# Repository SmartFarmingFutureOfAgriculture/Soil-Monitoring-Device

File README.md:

# Smart Farming Soil Monitoring Device
This is an **open-source soil monitoring system** designed to measure NPK levels, temperature, moisture, and conductivity.

🚧 **Project Status: In Development** 🚧  
This project is still in the **development phase** and may change frequently.  
Some features may not be fully implemented, and modifications are ongoing.  
Contributions and feedback are welcome!  

## License
- **Software**: GNU GPL-2.0  
- **Hardware**: CERN OHL  
- **Disclaimer**: This project is provided **"as is"**, without any warranty or liability.

## How to Contribute
Contributions are welcome! Please follow the licensing rules and give proper attribution.

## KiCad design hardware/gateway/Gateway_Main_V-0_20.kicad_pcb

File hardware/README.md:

## 🛠️ Hardware Development Tools
The hardware design files were created using:

- **KiCAD 6.x+** (for schematics & PCB design) → [https://www.kicad.org/](https://www.kicad.org/)
- **FreeCAD** (for 3D enclosure modeling) → [https://www.freecadweb.org/](https://www.freecadweb.org/)

💡 To modify the hardware, install **KiCAD** and **FreeCAD**, then open the project files.

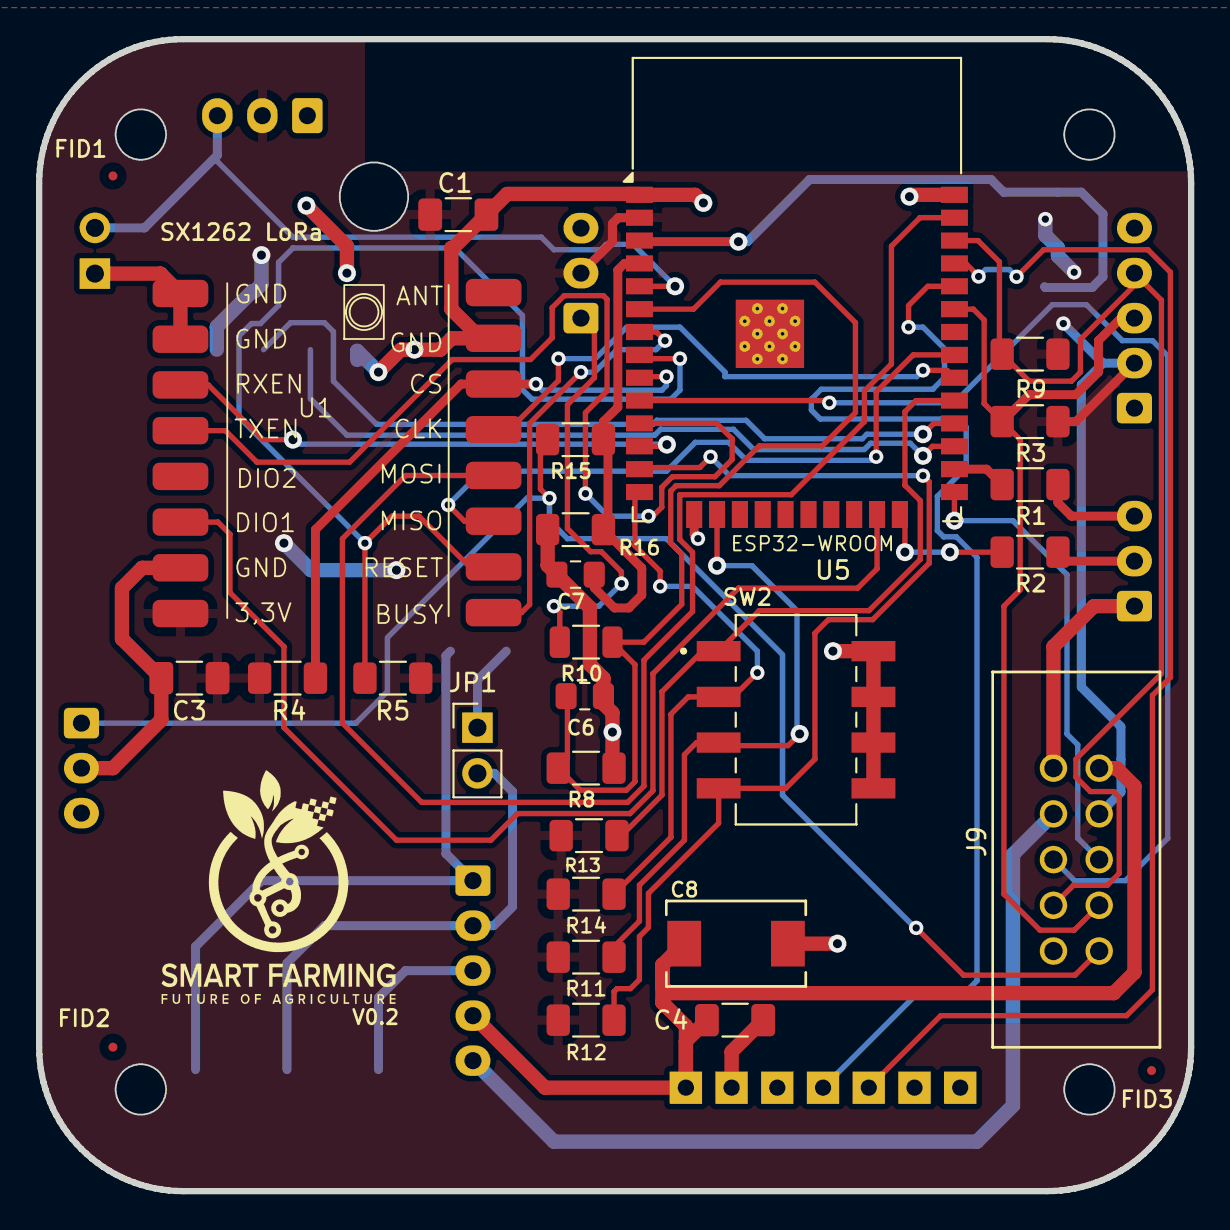
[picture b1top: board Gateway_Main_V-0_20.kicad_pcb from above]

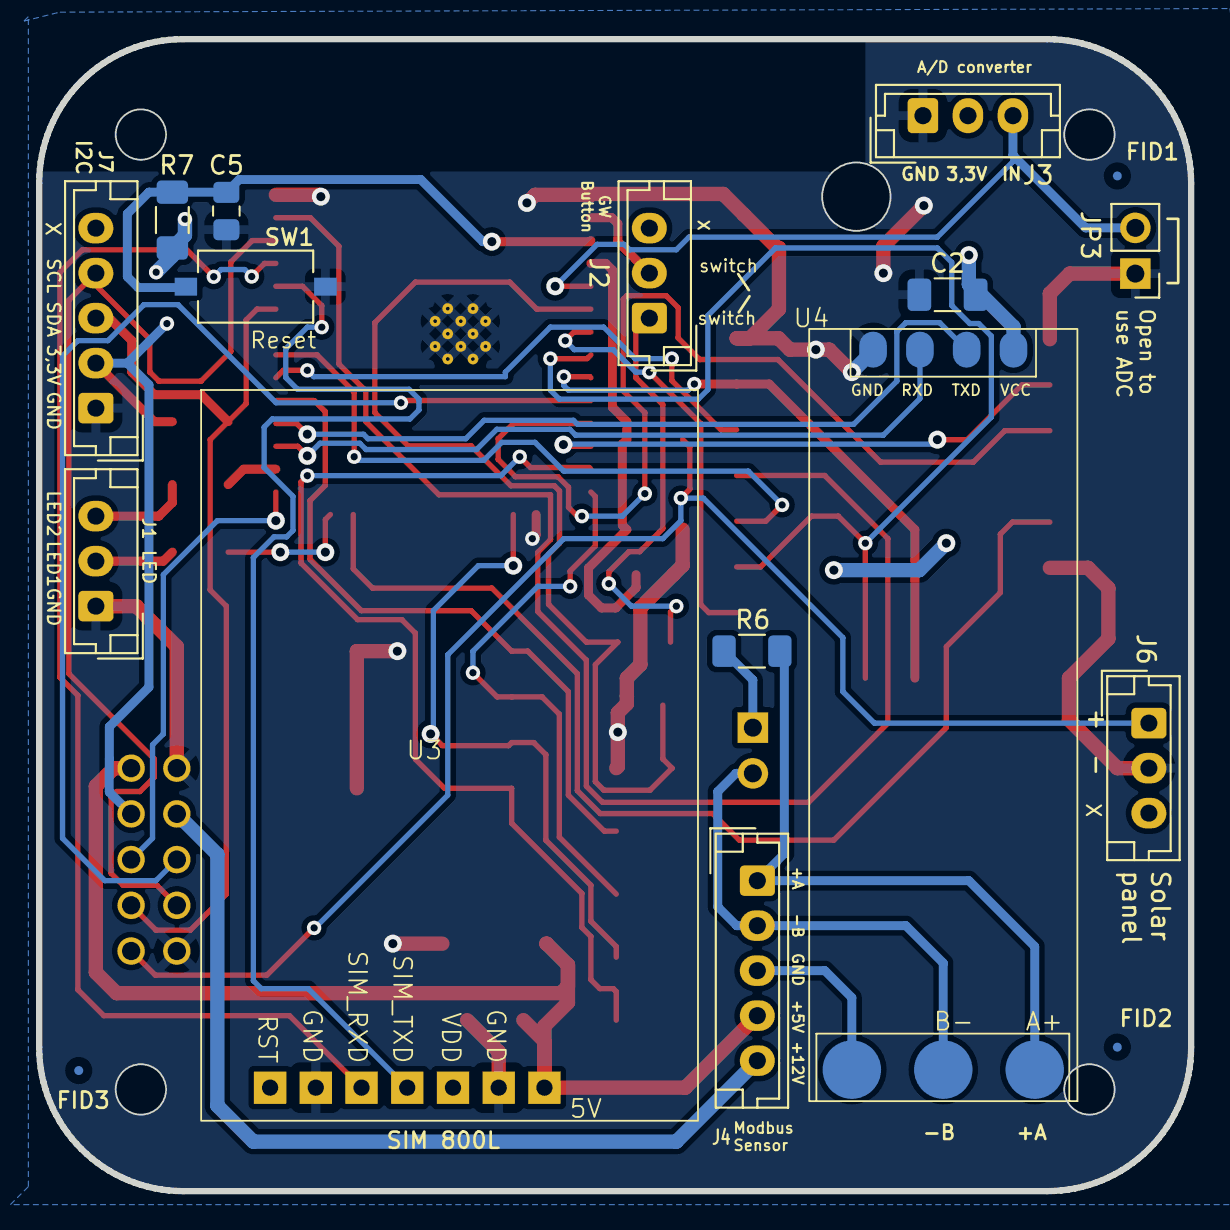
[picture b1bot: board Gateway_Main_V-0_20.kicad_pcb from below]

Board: 2 copper layers, 64.0 x 64.0 mm, 45 parts (17 on the bottom side), 39 nets.

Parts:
C1, C2, C3: 10uF X7R Ceramic; C_1206_3216Metric_Pad1.33x1.80mm_HandSolder
C4: 100uF; C_1206_3216Metric_Pad1.33x1.80mm_HandSolder
C5: 1uF; C_0805_2012Metric_Pad1.18x1.45mm_HandSolder
C6, C7: 0.1uF; C_0805_2012Metric_Pad1.18x1.45mm_HandSolder
C8: 470uF; TAJD_AVX
FID1, FID1#2, FID2, FID2#2, FID3, FID3#2: Fiducial; Fiducial_0.5mm_Mask1.5mm
J1: LED; JST_EH_B3B-EH-A_1x03_P2.50mm_Vertical
J2: Gateway button; JST_EH_B3B-EH-A_1x03_P2.50mm_Vertical
J3: A/D converter; JST_EH_B3B-EH-A_1x03_P2.50mm_Vertical
J4: Modbus (Sensor); JST_EH_B5B-EH-A_1x05_P2.50mm_Vertical
J6: Solar module; JST_EH_B3B-EH-A_1x03_P2.50mm_Vertical
J7: I2C; JST_EH_B5B-EH-A_1x05_P2.50mm_Vertical
J9: 302-S101; CONN10_302-S101_OST
JP1: Jumper_2_Bridged; PinHeader_1x02_P2.54mm_Vertical
JP3: ADC1_CH3; PinHeader_1x02_P2.54mm_Vertical
R1, R2: 150; R_1206_3216Metric_Pad1.30x1.75mm_HandSolder
R3, R9: 10k; R_1206_3216Metric_Pad1.30x1.75mm_HandSolder
R4, R5, R7: 47k; R_1206_3216Metric_Pad1.30x1.75mm_HandSolder
R6: 120; R_1206_3216Metric_Pad1.30x1.75mm_HandSolder
R8: 100k; R_1206_3216Metric_Pad1.30x1.75mm_HandSolder
R10: 47k; R_1206_3216Metric
R11, R12, R13, R14: 82k; R_1206_3216Metric_Pad1.30x1.75mm_HandSolder
R15: 20k 1%; R_1206_3216Metric_Pad1.30x1.75mm_HandSolder
R16: 30k 1%; R_1206_3216Metric_Pad1.30x1.75mm_HandSolder
SW1: Reset; SW_Tactile_SPST_NO_Straight_CK_PTS636Sx25SMTRLFS
SW2: SW-219-4MST; Switch-SW_219-4MST
U1: CORE1262-868M; SX1262_LoRa_NODE
U3: SIM800L; SIM800L_EVB-MODULE
U4: TTL to RS485; RS485_To_TTL
U5: ESP32-WROOM-32E; ESP32-WROOM-32D

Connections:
+3.3V: C1.1, C2.1, C3.1, J2.2, J3.2, J7.2, J9.7, R3.1, R4.1, R5.1, R7.1, R9.1, R11.1, R12.1, R13.1, R14.1, U1.8 (3V3), U4.4 (Vcc), U5.2 (VDD)
+5V: C4.1, C8.1, J4.4, J9.9, U3.1 (5V)
+12V: J4.5, J9.8
GND: C1.2, C2.2, C3.2, C4.2, C5.2, C6.2, C7.2, C8.2, J1.1, J3.1, J6.2, J7.1, J9.2, J9.10, JP3.1 (A), R8.2, R16.2, SW1.2, SW2.5, SW2.6, SW2.7, SW2.8, U1.1 (GND), U1.2 (GND), U1.7 (GND), U1.15 (GND), U3.2 (GND), U3.6 (GND), U4.1 (GND), U5.1 (GND), U5.15 (GND), U5.38 (GND), U5.39 (GND)
unnamed: J1.2, R2.2
unnamed: J1.3, R1.2
unnamed: J2.1, R10.1
unnamed: J3.3, JP3.2 (B), U5.5 (SENSOR_VN)
unnamed: J4.1, R6.2, U4.5 (A+)
unnamed: J4.2, JP1.2 (B), U4.6 (B-)
unnamed: J4.3, U4.7 (GND2)
unnamed: J6.1, J9.1, R15.1
unnamed: J7.3, J9.3, R3.2, U5.33 (IO21)
unnamed: J7.4, J9.4, R9.2, U5.36 (IO22)
unnamed: JP1.1 (A), R6.1
unnamed: U1.9 (BUSY), U5.7 (IO35)
unnamed: U1.13 (CLK), U5.30 (IO18)
unnamed: R4.2, U1.14 (CS), U5.9 (IO33)
unnamed: U1.6 (DIO1), U5.23 (IO15)
unnamed: U1.11 (MISO), U5.31 (IO19)
unnamed: U1.12 (MOSI), U5.37 (IO23)
unnamed: R5.2, U1.10 (RESET), U5.8 (IO32)
unnamed: U1.3 (RXEN), U5.12 (IO27)
unnamed: U1.4 (TXEN), U5.11 (IO26)
unnamed: U3.5 (SIM_RXD), U5.35 (TXD0/IO1)
unnamed: U3.4 (SIM_TXD), U5.34 (RXD0/IO3)
unnamed: U4.2 (RxD), U5.27 (IO16)
unnamed: U4.3 (TxD), U5.28 (IO17)
unnamed: C5.1, R7.2, SW1.1, U5.3 (EN)
unnamed: J9.5, U5.25 (IO0)
unnamed: R2.1, U5.24 (IO2)
unnamed: R1.1, U5.26 (IO4)
unnamed: R13.2, SW2.1, U5.29 (IO5)
unnamed: R14.2, SW2.2, U5.14 (IO12)
unnamed: R11.2, SW2.3, U5.16 (IO13)
unnamed: R12.2, SW2.4, U5.13 (IO14)
unnamed: J9.6, U5.10 (IO25)
unnamed: C6.1, R8.1, R10.2, U5.6 (IO34)
unnamed: C7.1, R15.2, R16.1, U5.4 (SENSOR_VP)

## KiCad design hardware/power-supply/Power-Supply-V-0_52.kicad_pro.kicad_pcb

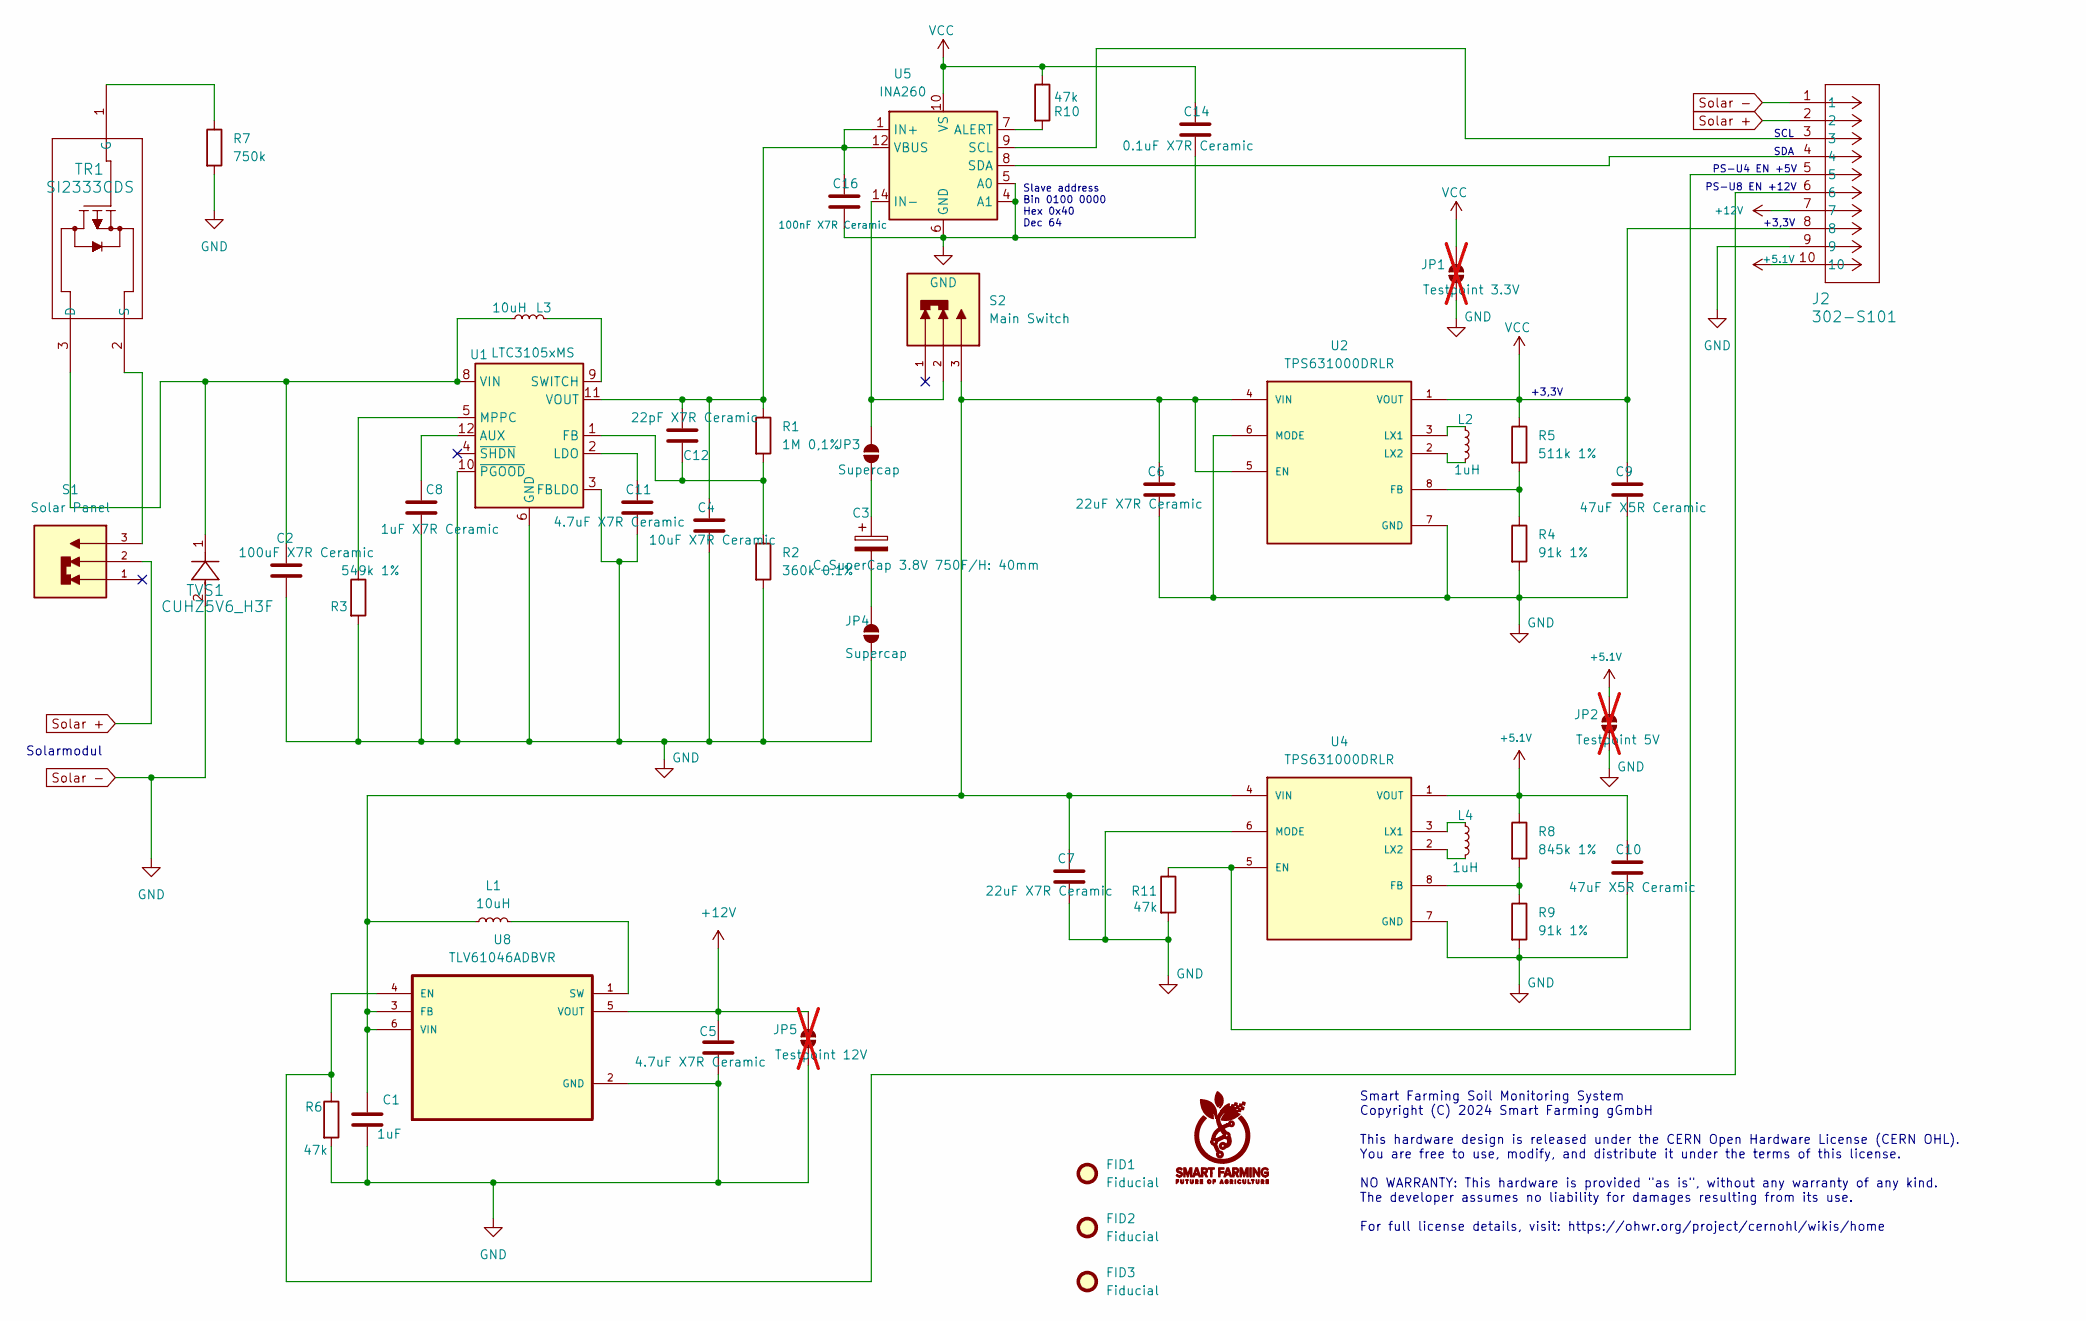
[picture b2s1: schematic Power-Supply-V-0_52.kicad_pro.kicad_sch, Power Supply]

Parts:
C1: 1uF; C_0805_2012Metric_Pad1.18x1.45mm_HandSolder
C2: 100uF X7R Ceramic; C_1206_3216Metric_Pad1.33x1.80mm_HandSolder
C3: C_SuperCap 3.8V 750F/H: 40mm; CP_Radial_D18.0mm_P7.50mm
C4: 10uF X7R Ceramic; C_1206_3216Metric_Pad1.33x1.80mm_HandSolder
C5, C11: 4.7uF X7R Ceramic; C_0805_2012Metric_Pad1.18x1.45mm_HandSolder
C6, C7: 22uF X7R Ceramic; C_1206_3216Metric_Pad1.33x1.80mm_HandSolder
C8: 1uF X7R Ceramic; C_0805_2012Metric_Pad1.18x1.45mm_HandSolder
C9, C10: 47uF X5R Ceramic; C_1206_3216Metric_Pad1.33x1.80mm_HandSolder
C12: 22pF X7R Ceramic; C_0805_2012Metric_Pad1.18x1.45mm_HandSolder
C14: 0.1uF X7R Ceramic; C_0805_2012Metric_Pad1.18x1.45mm_HandSolder
C16: 100nF X7R Ceramic; C_0805_2012Metric_Pad1.18x1.45mm_HandSolder
FID1, FID2, FID3: Fiducial; Fiducial_0.75mm_Mask1.5mm
J2: 302-S101; CONN10_302-S101_OST
JP1: Testpoint 3.3V; PinHeader_1x02_P2.54mm_Vertical; not fitted
JP2: Testpoint 5V; PinHeader_1x02_P2.54mm_Vertical; not fitted
JP3, JP4: Supercap; PinHeader_1x02_P2.54mm_Vertical
JP5: Testpoint 12V; PinHeader_1x02_P2.54mm_Vertical; not fitted
L1, L3: 10uH; L_Taiyo-Yuden_MD-5050
L2, L4: 1uH; L_1008_2520Metric_Pad1.43x2.20mm_HandSolder
R1: 1M 0,1%; R_1206_3216Metric_Pad1.30x1.75mm_HandSolder
R2: 360k 0.1%; R_1206_3216Metric_Pad1.30x1.75mm_HandSolder
R3: 549k 1%; R_1206_3216Metric_Pad1.30x1.75mm_HandSolder
R4, R9: 91k 1%; R_1206_3216Metric_Pad1.30x1.75mm_HandSolder
R5: 511k 1%; R_1206_3216Metric_Pad1.30x1.75mm_HandSolder
R6, R10, R11: 47k; R_1206_3216Metric_Pad1.30x1.75mm_HandSolder
R7: 750k; R_1206_3216Metric_Pad1.30x1.75mm_HandSolder
R8: 845k 1%; R_1206_3216Metric_Pad1.30x1.75mm_HandSolder
S1: Solar Panel; SW_JS102011SCQN; PARTREV 8 Oct 21
S2: Main Switch; SW_JS102011SCQN; PARTREV 8 Oct 21
TR1: SI2333CDS; TO-236_VIS
TVS1: CUHZ5V6_H3F; SOD-323HEUS2H_TOS
U1: LTC3105xMS; MSOP-12_3x4mm_P0.65mm
U2, U4: TPS631000DRLR; SOT-583-8; PARTREV B
U5: INA260; TSSOP-16_4.4x5mm_P0.65mm
U8: TLV61046ADBVR; SOT-23-6_Handsoldering

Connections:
+5.1V: C10.1, J2.10, JP2.2 (B), R8.1, U4.1 (VOUT)
+12V: C5.1, J2.7, JP5.2 (B), U8.5 (VOUT)
unnamed: C3.1, JP3.1 (A)
unnamed: JP3.2 (B), S2.2, U5.14 (IN-), U5.15 (IN-), U5.16 (IN-)
unnamed: C3.2, JP4.2 (B)
unnamed: C2.1, L3.1, TR1.3 (D), TVS1.1, U1.8 (VIN)
unnamed: R7.1, TR1.1 (G)
unnamed: S1.3, TR1.2 (S)
unnamed: C8.1, U1.12 (AUX)
unnamed: C12.2, R1.2, R2.1, U1.1 (FB)
unnamed: C11.1, U1.2 (LDO)
unnamed: R3.1, U1.5 (MPPC)
unnamed: L3.2, U1.9 (SWITCH)
unnamed: C4.1, C12.1, C16.1, R1.1, U1.11 (VOUT), U5.1 (IN+), U5.2 (IN+), U5.3 (IN+), U5.12 (VBUS)
unnamed: C1.1, C6.1, C7.1, L1.1, S2.3, U2.4 (VIN), U2.5 (EN), U4.4 (VIN), U8.3 (FB), U8.6 (VIN)
unnamed: R4.1, R5.2, U2.8 (FB)
unnamed: L2.1, U2.3 (LX1)
unnamed: L2.2, U2.2 (LX2)
unnamed: J2.5, R11.1, U4.5 (EN)
unnamed: R8.2, R9.1, U4.8 (FB)
unnamed: L4.1, U4.3 (LX1)
unnamed: L4.2, U4.2 (LX2)
unnamed: R10.2, U5.7 (ALERT)
unnamed: J2.3, U5.9 (SCL)
unnamed: J2.4, U5.8 (SDA)
unnamed: J2.6, R6.1, U8.4 (EN)
unnamed: L1.2, U8.1 (SW)
Solar +: J2.2, S1.2
Solar -: C1.2, C2.2, C4.2, C5.2, C6.2, C7.2, C8.2, C9.2, C10.2, C11.2, C14.2, C16.2, J2.1, J2.9, JP1.1 (A), JP2.1 (A), JP4.1 (A), JP5.1 (A), R2.2, R3.2, R4.2, R6.2, R7.2, R9.2, R11.2, TVS1.2, U1.3 (FBLDO), U1.6 (GND), U1.7 (GND), U1.10 (~PGOOD), U2.6 (MODE), U2.7 (GND), U4.6 (MODE), U4.7 (GND), U5.4 (A1), U5.5 (A0), U5.6 (GND), U5.11 (GND), U8.2 (GND)
VCC: C9.1, C14.1, J2.8, JP1.2 (B), R5.1, R10.1, U2.1 (VOUT), U5.10 (VS)

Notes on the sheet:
PS-U4 EN +5V
SCL
Smart Farming Soil Monitoring System Copyright (C) 2024 Smart Farming gGmbH This hardware design is released under the CERN Open Hardware License (CERN OHL). You are free to use, modify, and distribute it under the terms of this license. NO WARRANTY: This hardware is provided "as is", without any w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
Solarmodul
SDA
PS-U8 EN +12V
Slave address Bin 0100 0000 Hex 0x40 Dec 64
+3,3V

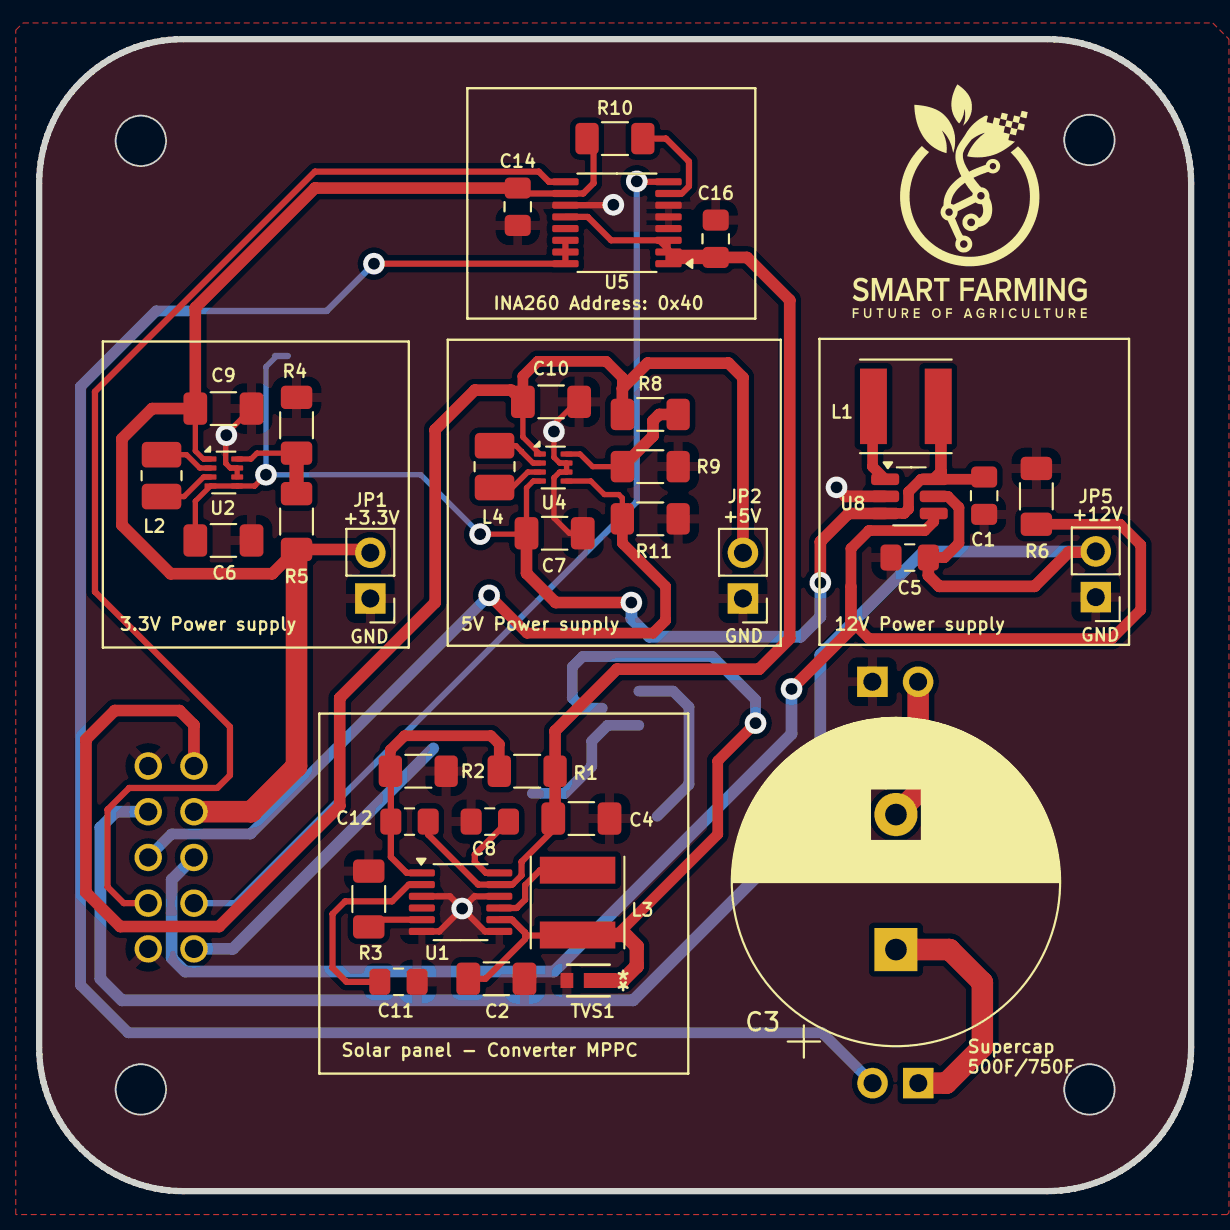
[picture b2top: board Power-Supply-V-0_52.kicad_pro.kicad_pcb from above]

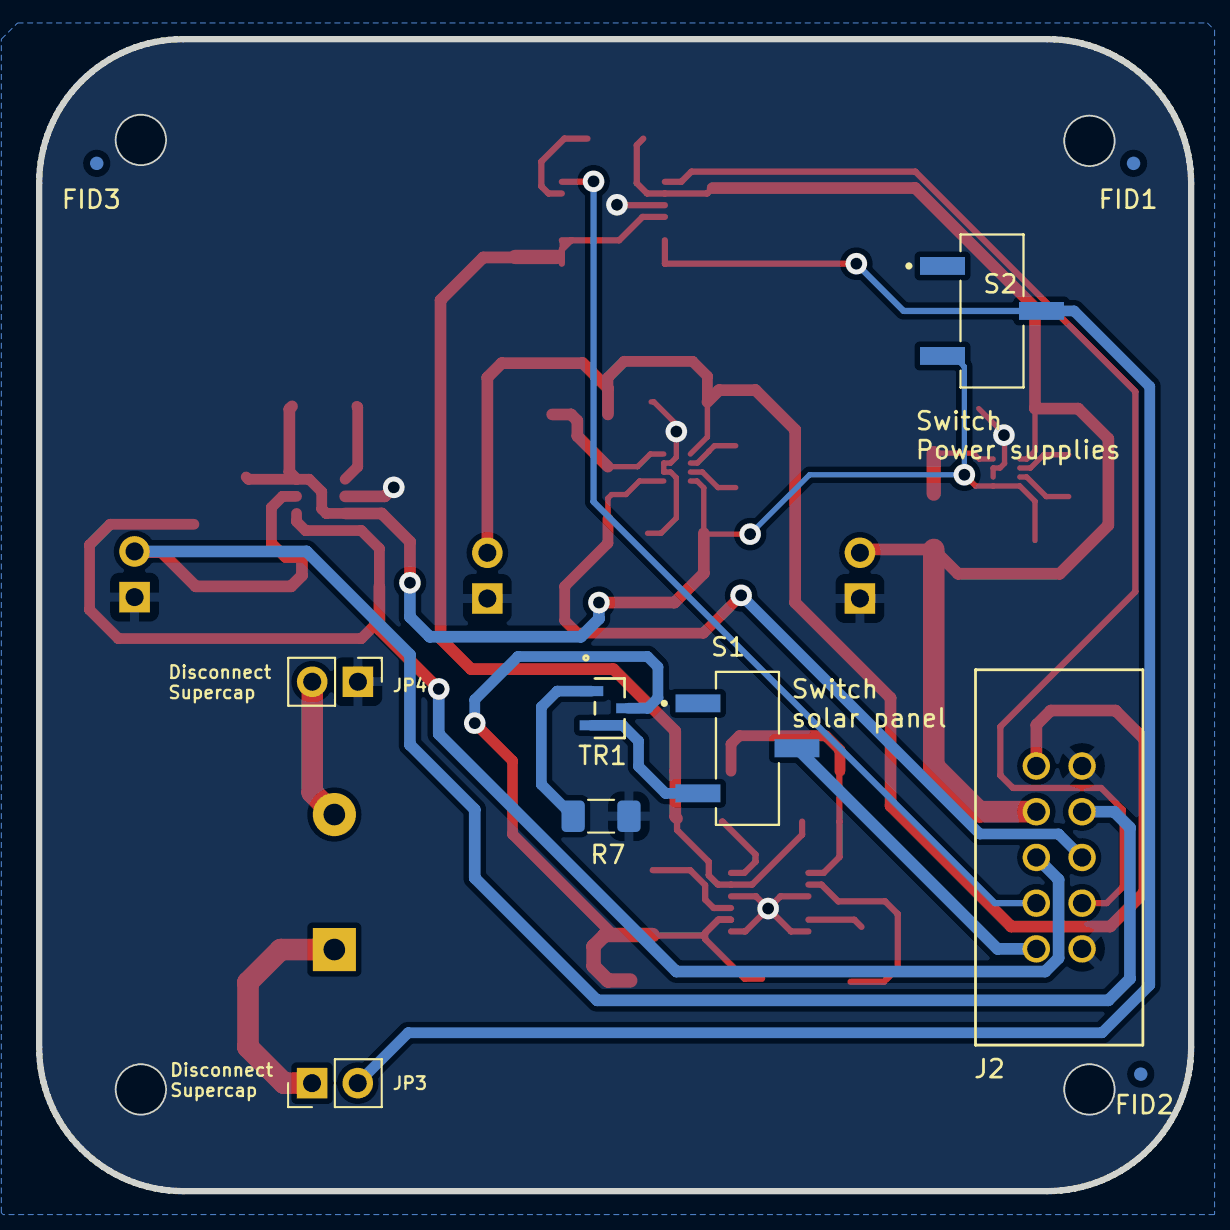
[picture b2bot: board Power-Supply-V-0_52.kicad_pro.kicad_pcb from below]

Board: 2 copper layers, 64.0 x 64.0 mm, 48 parts (10 on the bottom side), 30 nets.

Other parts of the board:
G**: LOGO; Logo_Smart_Farming

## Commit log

2025-03-10 Create LICENSE.txt
    Smart Farming Soil Monitoring System
    Copyright (C) 2024 Smart Farming gGmbH
    This hardware design is released under the CERN Open Hardware License (CERN OHL).
    You are free to use, modify, and distribute it under the terms of this license.
    NO WARRANTY: This hardware is provided "as is", without any warranty of any kind.
    The developer assumes no liability for damages resulting from its use.
2025-03-10 Create README.md
    Smart Farming Soil Monitoring System
    Copyright (C) 2024 Smart Farming gGmbH
    This hardware design is released under the CERN Open Hardware License (CERN OHL).
    You are free to use, modify, and distribute it under the terms of this license.
    NO WARRANTY: This hardware is provided "as is", without any warranty of any kind.
    The developer assumes no liability for damages resulting from its use.
2025-03-11 Create README.md
    The housing can be produced with a 3D printer. The hardware design files were created using:
    FreeCAD (for 3D enclosure modeling) → https://www.freecadweb.org/
    💡 To modify the hardware, install FreeCAD, then open the project files.
    Smart Farming Soil Monitoring System
    Copyright (C) 2024 Smart Farming gGmbH
    This hardware design is released under the CERN Open Hardware License (CERN OHL).
